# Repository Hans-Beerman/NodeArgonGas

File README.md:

**NodeArgonGas**

NodeArgonGas is a node, used at the MakerSpace Leiden, to verify the state of the Argon Gas bottle, used for welding at the MakerSpace.

See for more information about this node:

[https://wiki.makerspaceleiden.nl/mediawiki/index.php/Project\_Monitoring\_Gasflessen](https://wiki.makerspaceleiden.nl/mediawiki/index.php/Project_Monitoring_Gasflessen)

This repository has the following subdirs:

**Drawings:**

- A schematic drawing, showing the wiring between the PCB used for this node and the external components, like push buttons, the pressure sensor, the RFid reader etc. (in MS Visio, png and pdf format);
- A \*.jpg picture of the PCB;
- Specification of the box in which the PCB and the other components are installed;
- A state diagram of software for this node (in MS Visio and pdf format).

**KiCad\_files:**

The design of the PCB used for the Node/Controller. For this node the NodeStandard PCB V0.8 is used. With less and other components than described for the NodeStandard. The changes are given in the MS Excel file in the root of this directory. There are also 2 subdirectories:

- _NodeArgonGas:_ This directory contains the schematic drawing for the NodeArgonGas and the PCB as used for this node. The design of the PCB in this directory is only made to show how the components for the node are placed on the NodeStandard PCB.
- _NodeStandard:_ This directory contains the design of the NodeStandard V0.8.

**Photos:**

Some photos of the Node made.

**PlatformIO\_Files:**

The source code for the Node. For the development of this software PlatformIO is used, an Extension on Visual Studio Code.

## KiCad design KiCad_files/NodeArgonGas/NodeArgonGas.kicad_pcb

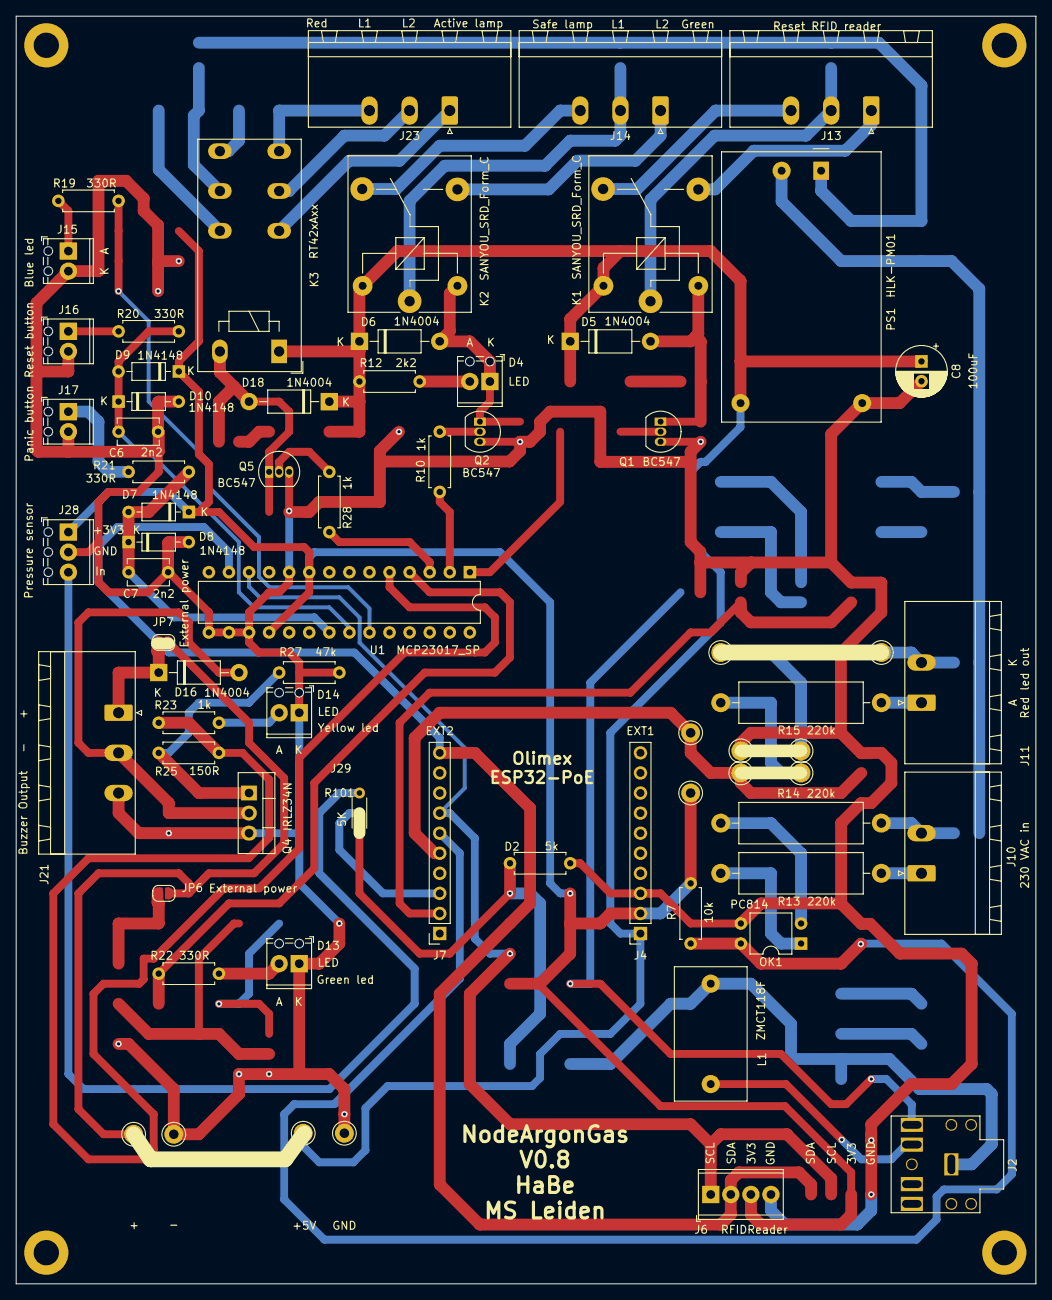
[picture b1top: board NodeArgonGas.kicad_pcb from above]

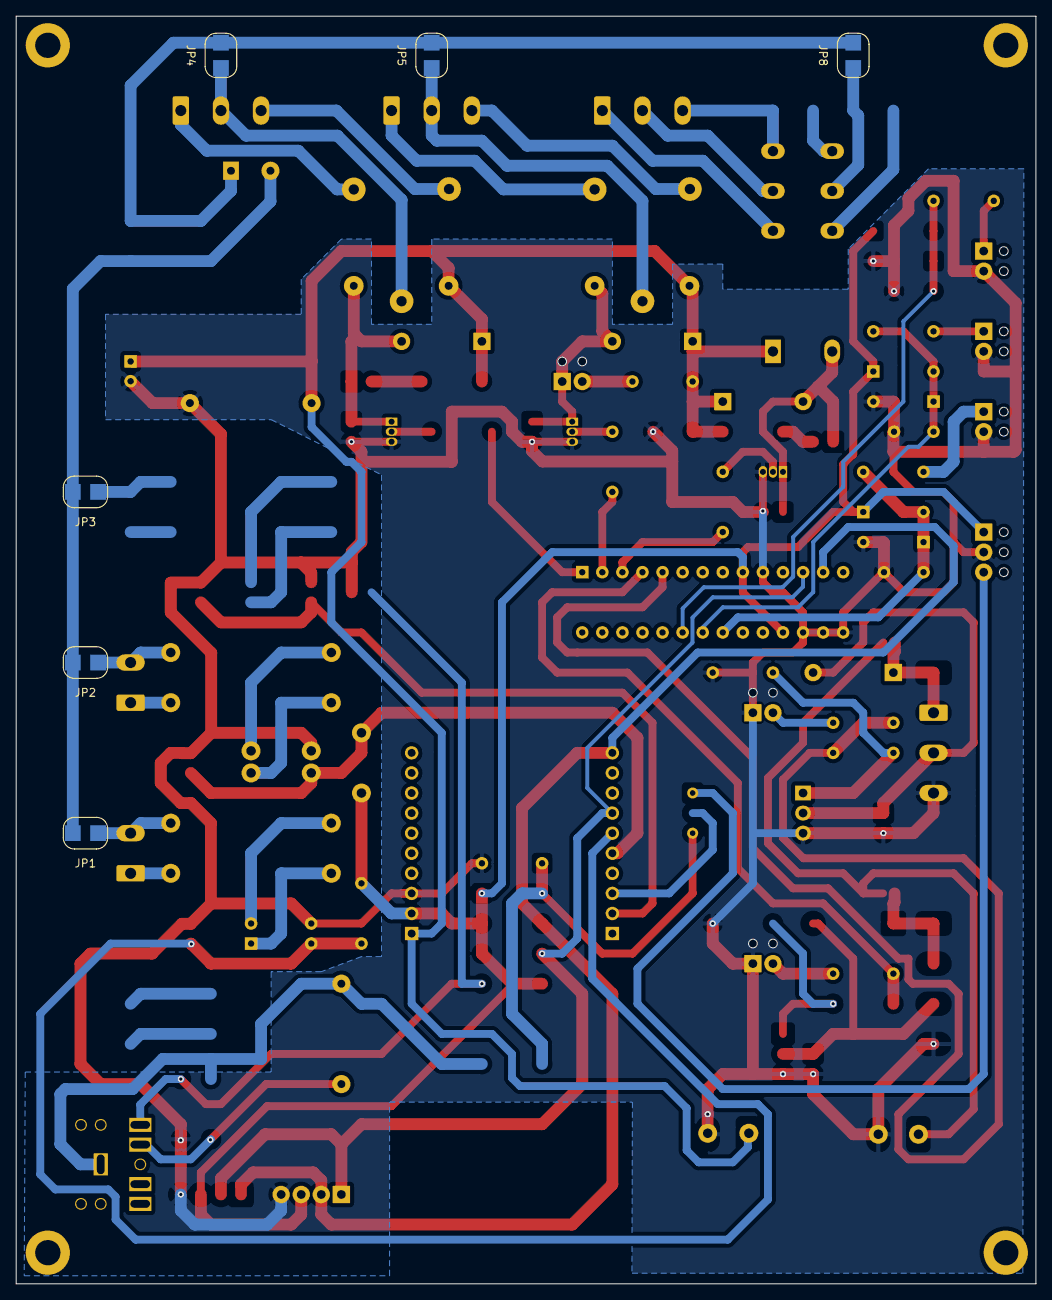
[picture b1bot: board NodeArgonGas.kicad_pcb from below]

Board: 2 copper layers, 129.0 x 160.4 mm, 63 parts (6 on the bottom side), 50 nets.

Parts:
C6, C7: 2n2; C_Disc_D5.1mm_W3.2mm_P5.00mm
C8: 100uF; CP_Radial_D6.3mm_P2.50mm
D2: 5k; R_Axial_DIN0207_L6.3mm_D2.5mm_P7.62mm_Horizontal
D4, D13, D14: LED; TerminalBlock_Phoenix_MPT-0,5-2-2.54_1x02_P2.54mm_Horizontal
D5, D6, D16, D18: 1N4004; D_DO-41_SOD81_P10.16mm_Horizontal
D7, D8, D9, D10: 1N4148; D_DO-35_SOD27_P7.62mm_Horizontal
J2: Current coil in; Jack_3.5mm_CUI_FEMPM_Horizontal
J4: EXT1; PinSocket_1x10_P2.54mm_Vertical
J6: RFIDReader; TerminalBlock_Phoenix_MPT-0,5-4-2.54_1x04_P2.54mm_Horizontal
J7: EXT2; PinSocket_1x10_P2.54mm_Vertical
J10: 230 VAC in; PhoenixContact_MSTB_2,5_2-GF-5,08_1x02_P5.08mm_Horizontal_T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
J11: Red led out; PhoenixContact_MSTB_2,5_2-GF-5,08_1x02_P5.08mm_Horizontal_T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
J13: Reset RFID reader; PhoenixContact_MSTB_2,5_3-GF-5,08_1x03_P5.08mm_Horizontal_T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
J14: Safe lamp L1 L2 Green; PhoenixContact_MSTB_2,5_3-GF-5,08_1x03_P5.08mm_Horizontal_T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
J15: Blue led; TerminalBlock_Phoenix_MPT-0,5-2-2.54_1x02_P2.54mm_Horizontal
J16: Reset button; TerminalBlock_Phoenix_MPT-0,5-2-2.54_1x02_P2.54mm_Horizontal
J17: Panic button; TerminalBlock_Phoenix_MPT-0,5-2-2.54_1x02_P2.54mm_Horizontal
J21: Buzzer Output - +; PhoenixContact_MSTB_2,5_3-GF-5,08_1x03_P5.08mm_Horizontal_T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
J23: Red L1 L2 Active lamp; PhoenixContact_MSTB_2,5_3-GF-5,08_1x03_P5.08mm_Horizontal_T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
J28: Pressure sensor; TerminalBlock_Phoenix_MPT-0,5-3-2.54_1x03_P2.54mm_Horizontal
J29: 5K; R_Axial_DIN0204_L3.6mm_D1.6mm_P5.08mm_Horizontal
JP1, JP2, JP3: 230VAC-N; SolderJumper-2_P3mm_Open_RoundedPad
JP4, JP5, JP8: 230VAC-L; SolderJumper-2_P3mm_Open_RoundedPad
JP6, JP7: External power; SolderJumper-2_P1.3mm_Open_RoundedPad1.0x1.5mm
K1, K2: SANYOU_SRD_Form_C; Relay_SPDT_SANYOU_SRD_Series_Form_C
K3: RT42xAxx; Relay_DPDT_Schrack-RT2-FormC_RM5mm
L1: ZMCT118F; TA12-100
OK1: PC814; DIP-4_W7.62mm
PS1: HLK-PM01; Converter_ACDC_HiLink_HLK-PMxx
Q1, Q2, Q5: BC547; TO-92_Inline
Q4: IRLZ34N; TO-220-3_Vertical
R7: 10k; R_Axial_DIN0207_L6.3mm_D2.5mm_P7.62mm_Horizontal
R10, R23, R28: 1k; R_Axial_DIN0207_L6.3mm_D2.5mm_P7.62mm_Horizontal
R12: 2k2; R_Axial_DIN0207_L6.3mm_D2.5mm_P7.62mm_Horizontal
R13, R14, R15: 220k; R_Axial_DIN0516_L15.5mm_D5.0mm_P20.32mm_Horizontal
R19, R20, R21, R22: 330R; R_Axial_DIN0207_L6.3mm_D2.5mm_P7.62mm_Horizontal
R25: 150R; R_Axial_DIN0207_L6.3mm_D2.5mm_P7.62mm_Horizontal
R27: 47k; R_Axial_DIN0207_L6.3mm_D2.5mm_P7.62mm_Horizontal
U1: MCP23017_SP; DIP-28_W7.62mm

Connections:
230VAC-L: JP4.2, JP5.2, JP8.2, PS1.1
230VAC-N: JP1.2, JP2.2, JP3.2, PS1.2
+3V3: D7.1, D9.1, J4.2, J6.3, J28.1, R7.1, U1.9, U1.18
+5V: C8.1, D5.1, D6.1, D18.1, J4.1, K1.5, K2.5, K3.A1, PS1.4, R12.1
ExternalDCPower: JP6.1, JP7.1
FET1: R22.1, U1.4
FET2: R23.1, R25.2, U1.5
GND: C6.2, C7.2, C8.2, D2.2, D8.2, D10.2, D13.1, D14.1, J4.3, J6.4, J15.2, J16.2, J17.2, J28.2, OK1.3, PS1.3, Q1.3, Q2.3, Q4.3, Q5.3, R27.2, U1.10, U1.15, U1.16, U1.17
GPI35: J7.3, J29.2
GPIO13_I2C-SDA: J6.2, J7.10, U1.13
GPIO16_I2C-SCL: J6.1, J7.7, U1.12
GPIO32: J7.6, OK1.4, R7.2
unnamed: D5.2, K1.2, Q1.1
unnamed: D4.1, D6.2, K2.2, Q2.1
unnamed: D4.2, R12.2
unnamed: D13.2, R22.2
unnamed: D14.2, R23.2
unnamed: D16.1, J21.1, J21.2, JP7.2
unnamed: D16.2, J21.3, Q4.2
unnamed: D18.2, K3.A2, Q5.1
unnamed: J2.S, L1.2
unnamed: J2.TN, L1.1
unnamed: J10.1, R13.1
unnamed: J10.2, JP1.1, R14.1
unnamed: J11.1, R15.1
unnamed: J11.2, JP2.1
unnamed: J13.1, K1.3
unnamed: J13.2, JP4.1, K1.1
unnamed: J13.3, K1.4
unnamed: J14.1, K2.3
unnamed: J14.2, JP5.1, K2.1
unnamed: J14.3, K2.4
unnamed: J15.1, R19.1
unnamed: J16.1, R20.1
unnamed: J17.1, R21.1
unnamed: J23.1, K3.12
unnamed: J23.2, K3.11
unnamed: J23.3, K3.14
unnamed: JP8.1, K3.21
unnamed: J28.3, J29.1
unnamed: OK1.1, R13.2
unnamed: OK1.2, R14.2
unnamed: Q2.2, R10.1
unnamed: Q4.1, R25.1, R27.1
unnamed: Q5.2, R28.1
Relay2: R10.2, U1.2
Relay3: R28.2, U1.3
Switch1: C7.1, D7.2, D8.1, R21.2, U1.21
Switch2: C6.1, D9.2, D10.1, R20.2, U1.22
Switch3: R19.2, U1.23

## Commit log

2021-08-05 Initial concept version V0.1.0.0
